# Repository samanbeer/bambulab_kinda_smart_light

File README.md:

# Kinda Smart Box s

---

## Project Overview

- **What is it?**  Its small box, which lets you control external light strip and external extruder fan. (Or anything that runs on 5-24V DC)

- **Why does it exist?** Coz  my old setup with mechanical swithces was a total mess and with this I can control the light from mobile from google Home! 

## Why I Made This

This was my old box. 

It was working great but i hated to always manualy turn lights or fan extruder...

So that why I creaed a small PCB for it, so it is not as messy as old setup, with ESP32-C3 and IRLZ44N mosfets that can control these peripherals. These are all the features:

1. **Very Smart:** Its connected to internet and it could be controlled anywhere from the world with google home or ESP RainMaker app from Espressif
2. **Fuse:** My printet can output maximum of 500mA so there is fuse pocket to protect printer if something bad happens.
3. **PWM:** Mechanical switches could only turn it ON and OFF. With this I can control the Exact Brightness i need for light or speed of the fan.

---

## Project Gallery

### 3D PCB Renders

### 3D Board Views

### PCB Layout & Schematic

### 3D Enclosure (Fusion 360)

*3D printable case is made in Fusion 360. All CAD files are in the CAD/ folder.*

---

## Assembly Guide

### Required Tools & Materials

- Soldering iron 
- Some good solder wire
- Solder flux 
- some good Tweezers for picking up these small Resisotrs and capacitors 
- 3D Printer (for printing case if you want

### Assembly Steps

1. **Start with small components:**
   - All resistors.
   - Just use tweeters and solder 1 pin, check if its correctly alligned and then solder the second :D (Some rezistors are at the bottom side of PCB - Dont forget about them)
2. **LED and DIODES:**
   - Solder the red led but and make sure it has correct polarity.
   - Also solder the 2 1N4007 diodes vertiacaly and make sure th polarity is correct. Otherwise some bad things will happen :|
3. **Mosfets**
   - Solder both mosfets (also with correct orientation ofcourse) and cut the legs under the board so they fit in case
4. **Final:**
   - Place the PCB into the case.
5- DONE

---

## Firmware & Software Setup

###### 1. Arduino IDE Setup

- Install the **esp32** package by Espressif in Boards Manager.

- **Board:** XIAO_ESP32C3

- **Partition Scheme:** RainMaker 4MB  (**IMPORTANT**)

- **USB CDC On Boot:** Enabled

### 2. Flashing XIAO ESP32-C3

- Connect XIAO ESP32-C3 to PC and select the correct COM port in arduino IDE.

- Open `Firmware/code/code.ino` and click **Upload**.

- The red LED turns ON (waiting for Wi-Fi connection).

### 3. Pairing & Google Home Integration

- Open the **ESP RainMaker** app -> tap **+ Add Device** -> **BLE**.

- Select **`PROV_XIAO_SWITCH`**, enter PIN **`12345678`**, and select your Wi-Fi in list.

- The red LED turns OFF once connected; **Bambu Light** and **Bambu Extruder Fan** appear in the app.

- In the **Google Home** app: go to **Devices** -> **+ Add** -> **Works with Google** -> link your **ESP RainMaker** account.

## Bill of Materials

| Reference    | Qty | Value                | Footprint                                                             | link                                                                                                                         | Cost ($)  |
|:------------ |:---:|:-------------------- |:--------------------------------------------------------------------- | ---------------------------------------------------------------------------------------------------------------------------- | --------- |
| D1, D2       | 2   | 1N4007               | Diode_THT:D_DO-41_SOD81_P2.54mm_Vertical_AnodeUp                      | [TME.eu](https://www.tme.eu/cz/details/1n5819-dio/diody-schottky-tht/diotec-semiconductor/1n5819/)                           | 0,62 $    |
| D3           | 1   | LED                  | LED_THT:LED_D3.0mm                                                    | [TME.eu](https://www.tme.eu/cz/details/l-934lid/diody-led-tht-kulate/kingbright-electronic/)                                 | 0.11      |
| J1, J2       | 2   | Screw_Terminal_01x02 | TerminalBlock_RND:TerminalBlock_RND_205-00001_1x02_P5.00mm_Horizontal | [TME.eu](https://www.tme.eu/cz/en/details/dg301-5.0-2p12/pcb-terminal-blocks/degson-electronics/dg301-5-0-02p-12-00a-h/)     | 0.44      |
| J3           | 1   | INPUT__DC_JACK_24V   | Connector that will be mounted to CASE and wired by wire to PCB       | [TME.eu](https://www.tme.eu/cz/en/details/pc-gm2.5/dc-power-connectors/ninigi/)                                              | 4.24      |
| J4           | 1   | FUSE_500mA           | Connector that will be mounted to CASE and wired by wire to PCB       | [TME.eu](https://www.tme.eu/cz/en/details/r3-12e/panel-mount-fuseholders/sci/)                                               | 2.27      |
| Q1, Q2       | 2   | IRLZ44N              | Package_TO_SOT_THT:TO-220-3_Vertical                                  | [TME.eu](https://www.tme.eu/cz/en/details/irlz44npbf/tht-n-channel-transistors/infineon-technologies/)                       | 3.75      |
| R1, R4       | 2   | 100R                 | Resistor_SMD:R_0805_2012Metric_Pad1.20x1.40mm_HandSolder              | [TME.eu](https://www.tme.eu/cz/en/details/crcw0805100rfktabc/smd-resistors/vishay/)                                          | 0.027     |
| R2, R3       | 2   | 10k                  | Resistor_SMD:R_0805_2012Metric_Pad1.20x1.40mm_HandSolder              | [TME.eu](https://www.tme.eu/cz/en/details/crcw080510k0fkea/smd-resistors/vishay/)                                            | 0.027     |
| R6           | 1   | 1k                   | Resistor_SMD:R_0805_2012Metric_Pad1.20x1.40mm_HandSolder              | [TME.eu](https://www.tme.eu/cz/en/details/rc0805fr-071k/smd-resistors/yageo/rc0805fr-071kl/)                                 | 0.068     |
| SW1, SW2     | 2   | SW_SPDT              | Connector_PinSocket_2.54mm:PinSocket_1x03_P2.54mm_Vertical            | [TME.eu](https://www.tme.eu/cz/en/details/bsi-10/slide-switches/sungmun-electronics/ssi-10/)                                 | 1.40      |
| U1           | 1   | XIAO-ESP32-C3-SMD    | Seeed_Studio_XIAO_Series:XIAO-ESP32-C3-SMD                            | [TME.eu](https://www.tme.eu/cz/en/details/seeed-113991054/development-kits-for-data-transmission/seeed-studio/xiao-esp32c3/) | 7.71      |
| PCB          |     |                      |                                                                       | jlcpcb.com                                                                                                                   | 9.45      |
| Shipping TME |     |                      |                                                                       |                                                                                                                              | 7.76      |
| **TOTAL**    |     |                      |                                                                       |                                                                                                                              | **37.87** |

> Btw you can import every components that is from TME directly to TME cart with this file: [quick_order_TME.csv](PCB/quick_order_TME.csv) 

---

## How to Use

1. **Power:** Connect 12-24V power supply do DC JACK and 5V UCBC
2. **Wifi:** Wait a few second and it will automatically connect to wifi (after first setup)
3. **Use it :D** now you can say: "Hey google, Turn on my light on printer."  

---

- Designed by **Šámot** in [Hack Club Forge](https://forge.hackclub.com/projects/3035) project.

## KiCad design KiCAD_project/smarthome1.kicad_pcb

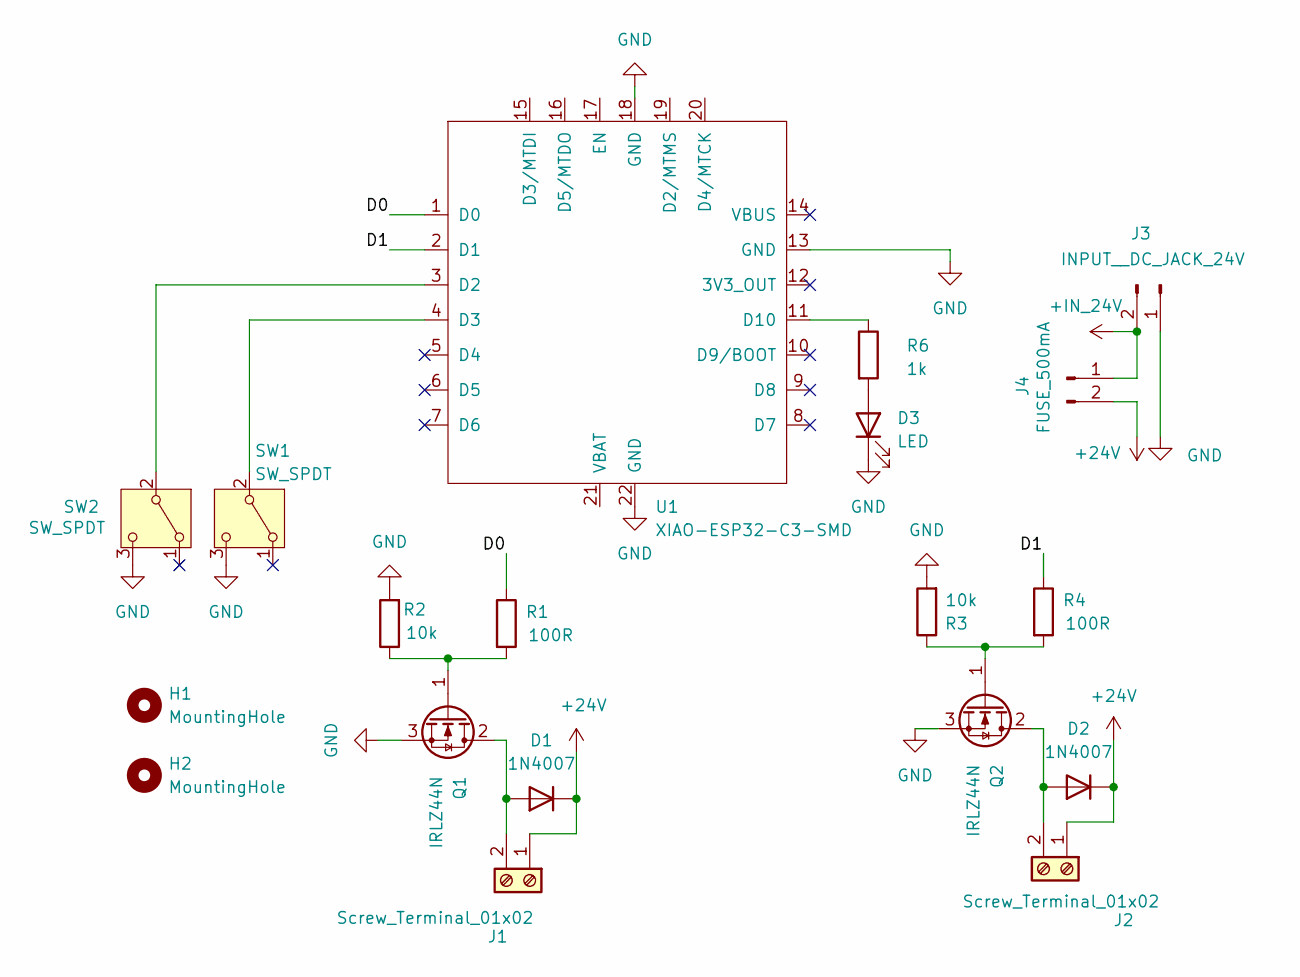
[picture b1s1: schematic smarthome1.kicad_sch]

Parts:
D1, D2: 1N4007; D_DO-41_SOD81_P2.54mm_Vertical_AnodeUp
D3: LED; LED_D3.0mm
H1, H2: MountingHole; MountingHole_2.5mm
J1, J2: Screw_Terminal_01x02; TerminalBlock_RND_205-00001_1x02_P5.00mm_Horizontal
J3: INPUT__DC_JACK_24V; AMASS_XT30U-F_1x02_P5.0mm_Vertical
J4: FUSE_500mA; AMASS_XT30U-F_1x02_P5.0mm_Vertical
Q1, Q2: IRLZ44N; TO-220-3_Vertical
R1, R4: 100R; R_0805_2012Metric_Pad1.20x1.40mm_HandSolder
R2, R3: 10k; R_0805_2012Metric_Pad1.20x1.40mm_HandSolder
R6: 1k; R_0805_2012Metric_Pad1.20x1.40mm_HandSolder
SW1, SW2: SW_SPDT; PinSocket_1x03_P2.54mm_Vertical
U1: XIAO-ESP32-C3-SMD

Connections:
+24V: D1.1 (K), D2.1 (K), J1.1, J2.1, J4.2
+IN_24V: J3.2, J4.1
/D0: R1.1, U1.1 (D0)
/D1: R4.1, U1.2 (D1)
GND: D3.1 (K), J3.1, Q1.3 (S), Q2.3 (S), R2.2, R3.2, SW1.3 (C), SW2.3 (C), U1.13 (GND), U1.18 (GND), U1.22 (GND)
unnamed: D1.2 (A), J1.2, Q1.2 (D)
unnamed: D2.2 (A), J2.2, Q2.2 (D)
unnamed: D3.2 (A), R6.2
unnamed: Q1.1 (G), R1.2, R2.1
unnamed: Q2.1 (G), R3.1, R4.2
unnamed: SW1.2 (B), U1.4 (D3)
unnamed: SW2.2 (B), U1.3 (D2)
unnamed: R6.1, U1.11 (D10)

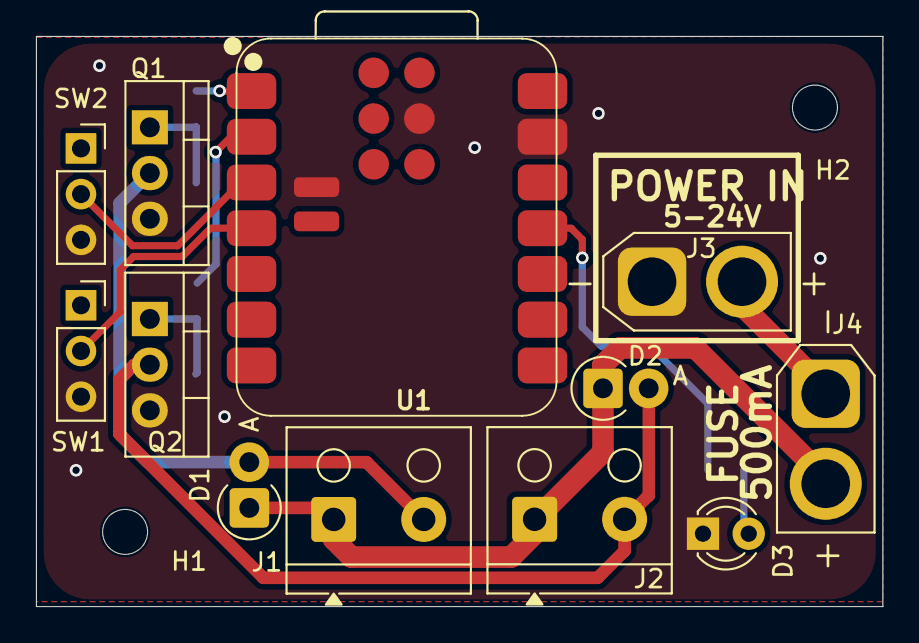
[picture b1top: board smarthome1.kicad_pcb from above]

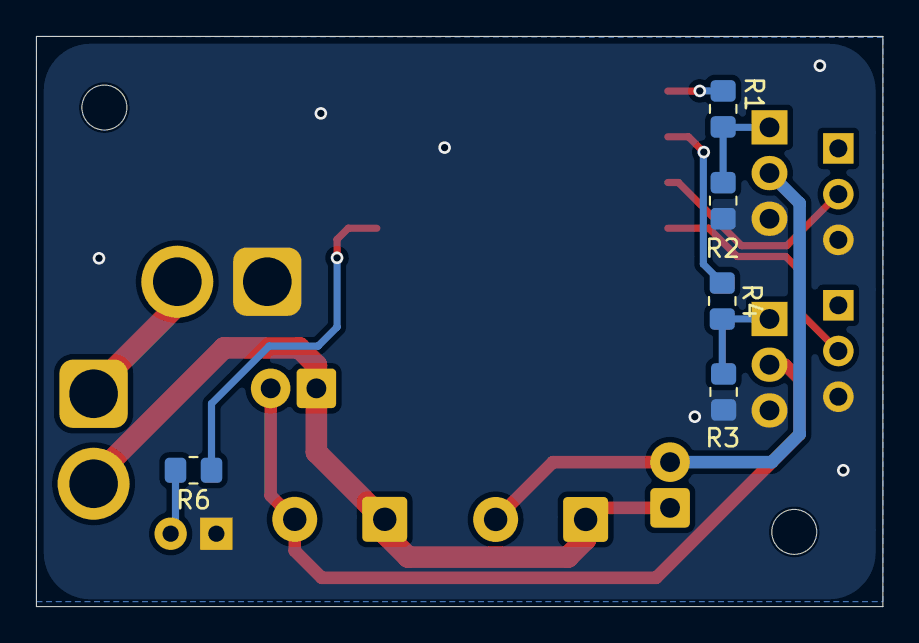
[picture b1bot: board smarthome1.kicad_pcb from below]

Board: 2 copper layers, 47.0 x 31.7 mm, 19 parts (5 on the bottom side), 13 nets.

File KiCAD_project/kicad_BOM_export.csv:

"Reference","Qty","Value","Footprint"
"D1,D2","2","1N4007","Diode_THT:D_DO-41_SOD81_P2.54mm_Vertical_AnodeUp"
"D3","1","LED","LED_THT:LED_D3.0mm"
"J1,J2","2","Screw_Terminal_01x02","TerminalBlock_RND:TerminalBlock_RND_205-00001_1x02_P5.00mm_Horizontal"
"J3","1","INPUT__DC_JACK_24V","Connector_AMASS:AMASS_XT30U-F_1x02_P5.0mm_Vertical"
"J4","1","FUSE_500mA","Connector_AMASS:AMASS_XT30U-F_1x02_P5.0mm_Vertical"
"Q1,Q2","2","IRLZ44N","Package_TO_SOT_THT:TO-220-3_Vertical"
"R1,R4","2","100R","Resistor_SMD:R_0805_2012Metric_Pad1.20x1.40mm_HandSolder"
"R2,R3","2","10k","Resistor_SMD:R_0805_2012Metric_Pad1.20x1.40mm_HandSolder"
"R6","1","1k","Resistor_SMD:R_0805_2012Metric_Pad1.20x1.40mm_HandSolder"
"SW1,SW2","2","SW_SPDT","Connector_PinSocket_2.54mm:PinSocket_1x03_P2.54mm_Vertical"
"U1","1","XIAO-ESP32-C3-SMD","Seeed_Studio_XIAO_Series:XIAO-ESP32-C3-SMD"
